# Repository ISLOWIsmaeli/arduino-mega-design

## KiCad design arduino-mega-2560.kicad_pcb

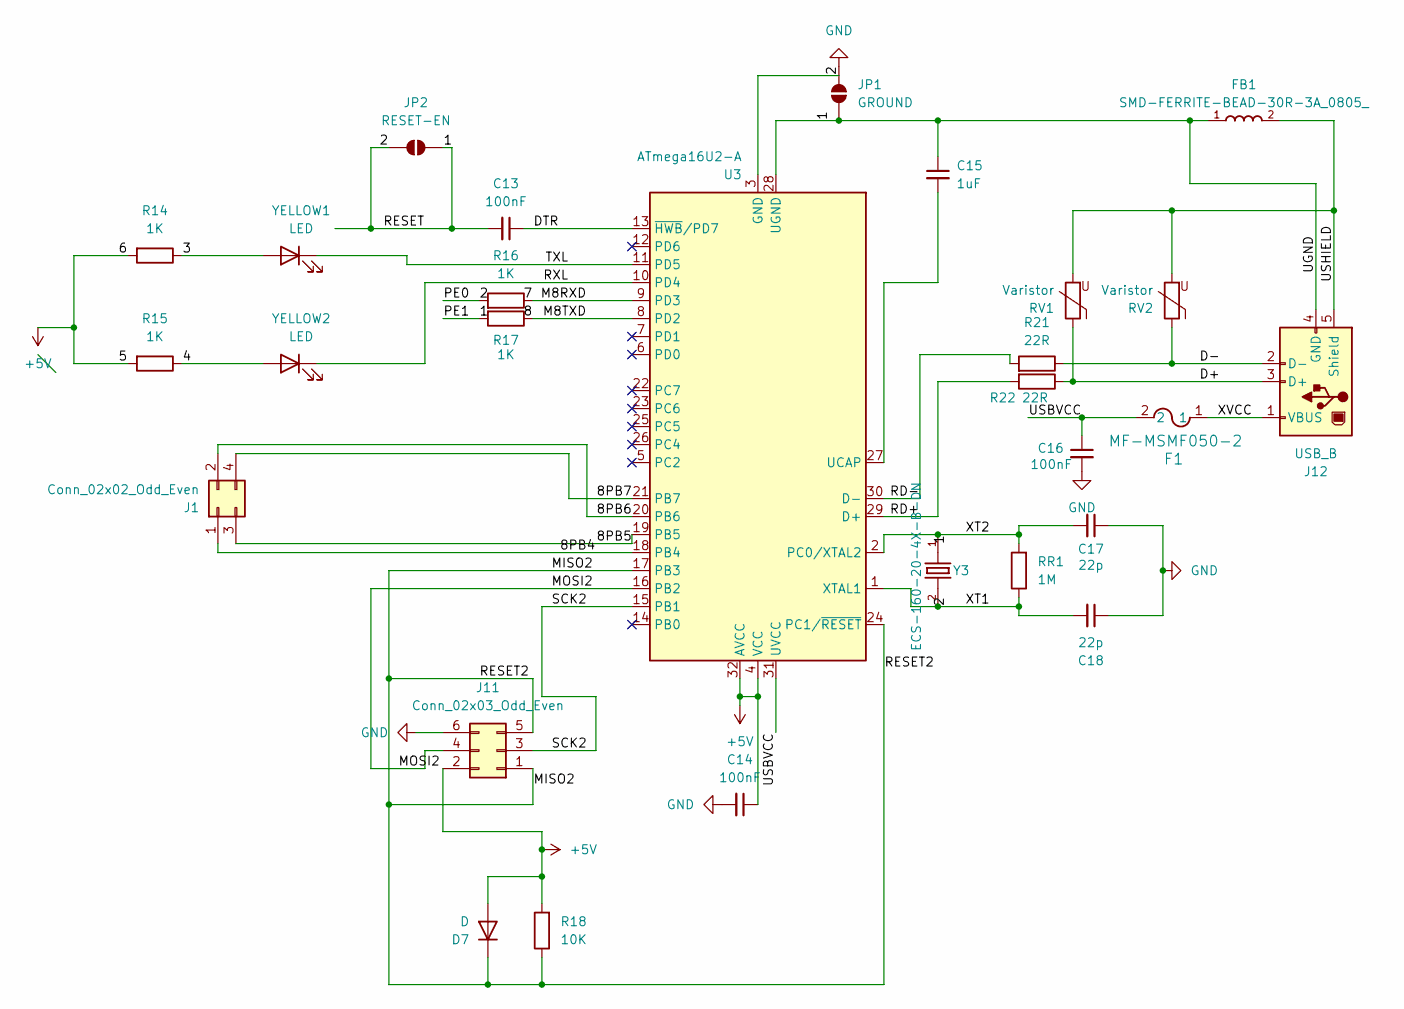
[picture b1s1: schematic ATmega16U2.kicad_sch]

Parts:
C13, C14, C16: 100nF; C_0402_1005Metric_Pad0.74x0.62mm_HandSolder
C15: 1uF; C_0402_1005Metric_Pad0.74x0.62mm_HandSolder
C17, C18: 22p; C_0402_1005Metric_Pad0.74x0.62mm_HandSolder
D7: D; D_0603_1608Metric
F1: MF-MSMF050-2; FUSE_F050-2
FB1: SMD-FERRITE-BEAD-30R-3A_0805_; L0805; MPN MH2029-300Y
J1: Conn_02x02_Odd_Even; PinHeader_2x02_P1.00mm_Vertical
J11: Conn_02x03_Odd_Even; PinHeader_2x03_P1.00mm_Vertical
J12: USB_B; USB_B_OST_USB-B1HSxx_Horizontal
JP1: GROUND; SolderJumper-2_P1.3mm_Open_RoundedPad1.0x1.5mm
JP2: RESET-EN; SolderJumper-2_P1.3mm_Open_RoundedPad1.0x1.5mm
R14, R15, R16, R17: 1K; R_0201_0603Metric_Pad0.64x0.40mm_HandSolder
R18: 10K; R_0201_0603Metric_Pad0.64x0.40mm_HandSolder
R21, R22: 22R; R_0201_0603Metric_Pad0.64x0.40mm_HandSolder
RR1: 1M; R_0201_0603Metric_Pad0.64x0.40mm_HandSolder
RV1, RV2: Varistor; R_0201_0603Metric_Pad0.64x0.40mm_HandSolder
U3: ATmega16U2-A; TQFP-32_7x7mm_P0.8mm
Y3: ECS-160-20-4X-B-DN; XTAL_ECS-160-20-4X-B-DN
YELLOW1, YELLOW2: LED; LED_0201_0603Metric

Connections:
+5V: C14.1, D7.2 (A), J11.2, R14.2, R15.2, R18.2, U3.4 (VCC), U3.32 (AVCC); also elsewhere on the board
/ATmega16U2/1: C13.2, C15.1, C17.2, C18.2, FB1.1, J12.4 (GND), JP1.1 (A), JP2.1 (A), JP2.2 (B), R16.2, R17.2, RR1.1, RR1.2, U3.1 (XTAL1), U3.2 (PC0/XTAL2), U3.3 (GND), U3.28 (UGND), Y3.1, Y3.2; also elsewhere on the board
/ATmega16U2/3: R14.1, YELLOW1.2 (A)
/ATmega16U2/4: R15.1, YELLOW2.2 (A)
/ATmega16U2/7: R16.1, U3.9 (PD3)
/ATmega16U2/8: R17.1, U3.8 (PD2)
/ATmega16U2/8PB4: J1.1, U3.18 (PB4)
/ATmega16U2/8PB5: J1.3, U3.19 (PB5)
/ATmega16U2/8PB6: J1.2, U3.20 (PB6)
/ATmega16U2/8PB7: J1.4, U3.21 (PB7)
/ATmega16U2/D+: J12.3 (D+), R22.1, RV1.1
/ATmega16U2/D-: J12.2 (D-), R21.1, RV2.1
/ATmega16U2/DTR: C13.1, U3.13 (~HWB/PD7)
/ATmega16U2/MISO2: D7.1 (K), J11.1, J11.5, R18.1, U3.17 (PB3), U3.24 (PC1/~RESET)
/ATmega16U2/MOSI2: J11.4, U3.16 (PB2)
/ATmega16U2/RD+: R22.2, U3.29 (D+)
/ATmega16U2/RD-: R21.2, U3.30 (D-)
/ATmega16U2/RXL: U3.10 (PD4), YELLOW2.1 (K)
/ATmega16U2/SCK2: J11.3, U3.15 (PB1)
/ATmega16U2/TXL: U3.11 (PD5), YELLOW1.1 (K)
/ATmega16U2/USBVCC: C16.1, F1.2, U3.31 (UVCC)
/ATmega16U2/USHIELD: FB1.2, J12.5 (Shield), RV1.2, RV2.2
/ATmega16U2/XVCC: F1.1, J12.1 (VBUS)
GND: C14.2, C16.2, C17.1, C18.1, J11.6, JP1.2 (B); also elsewhere on the board
unnamed: C15.2, U3.27 (UCAP)

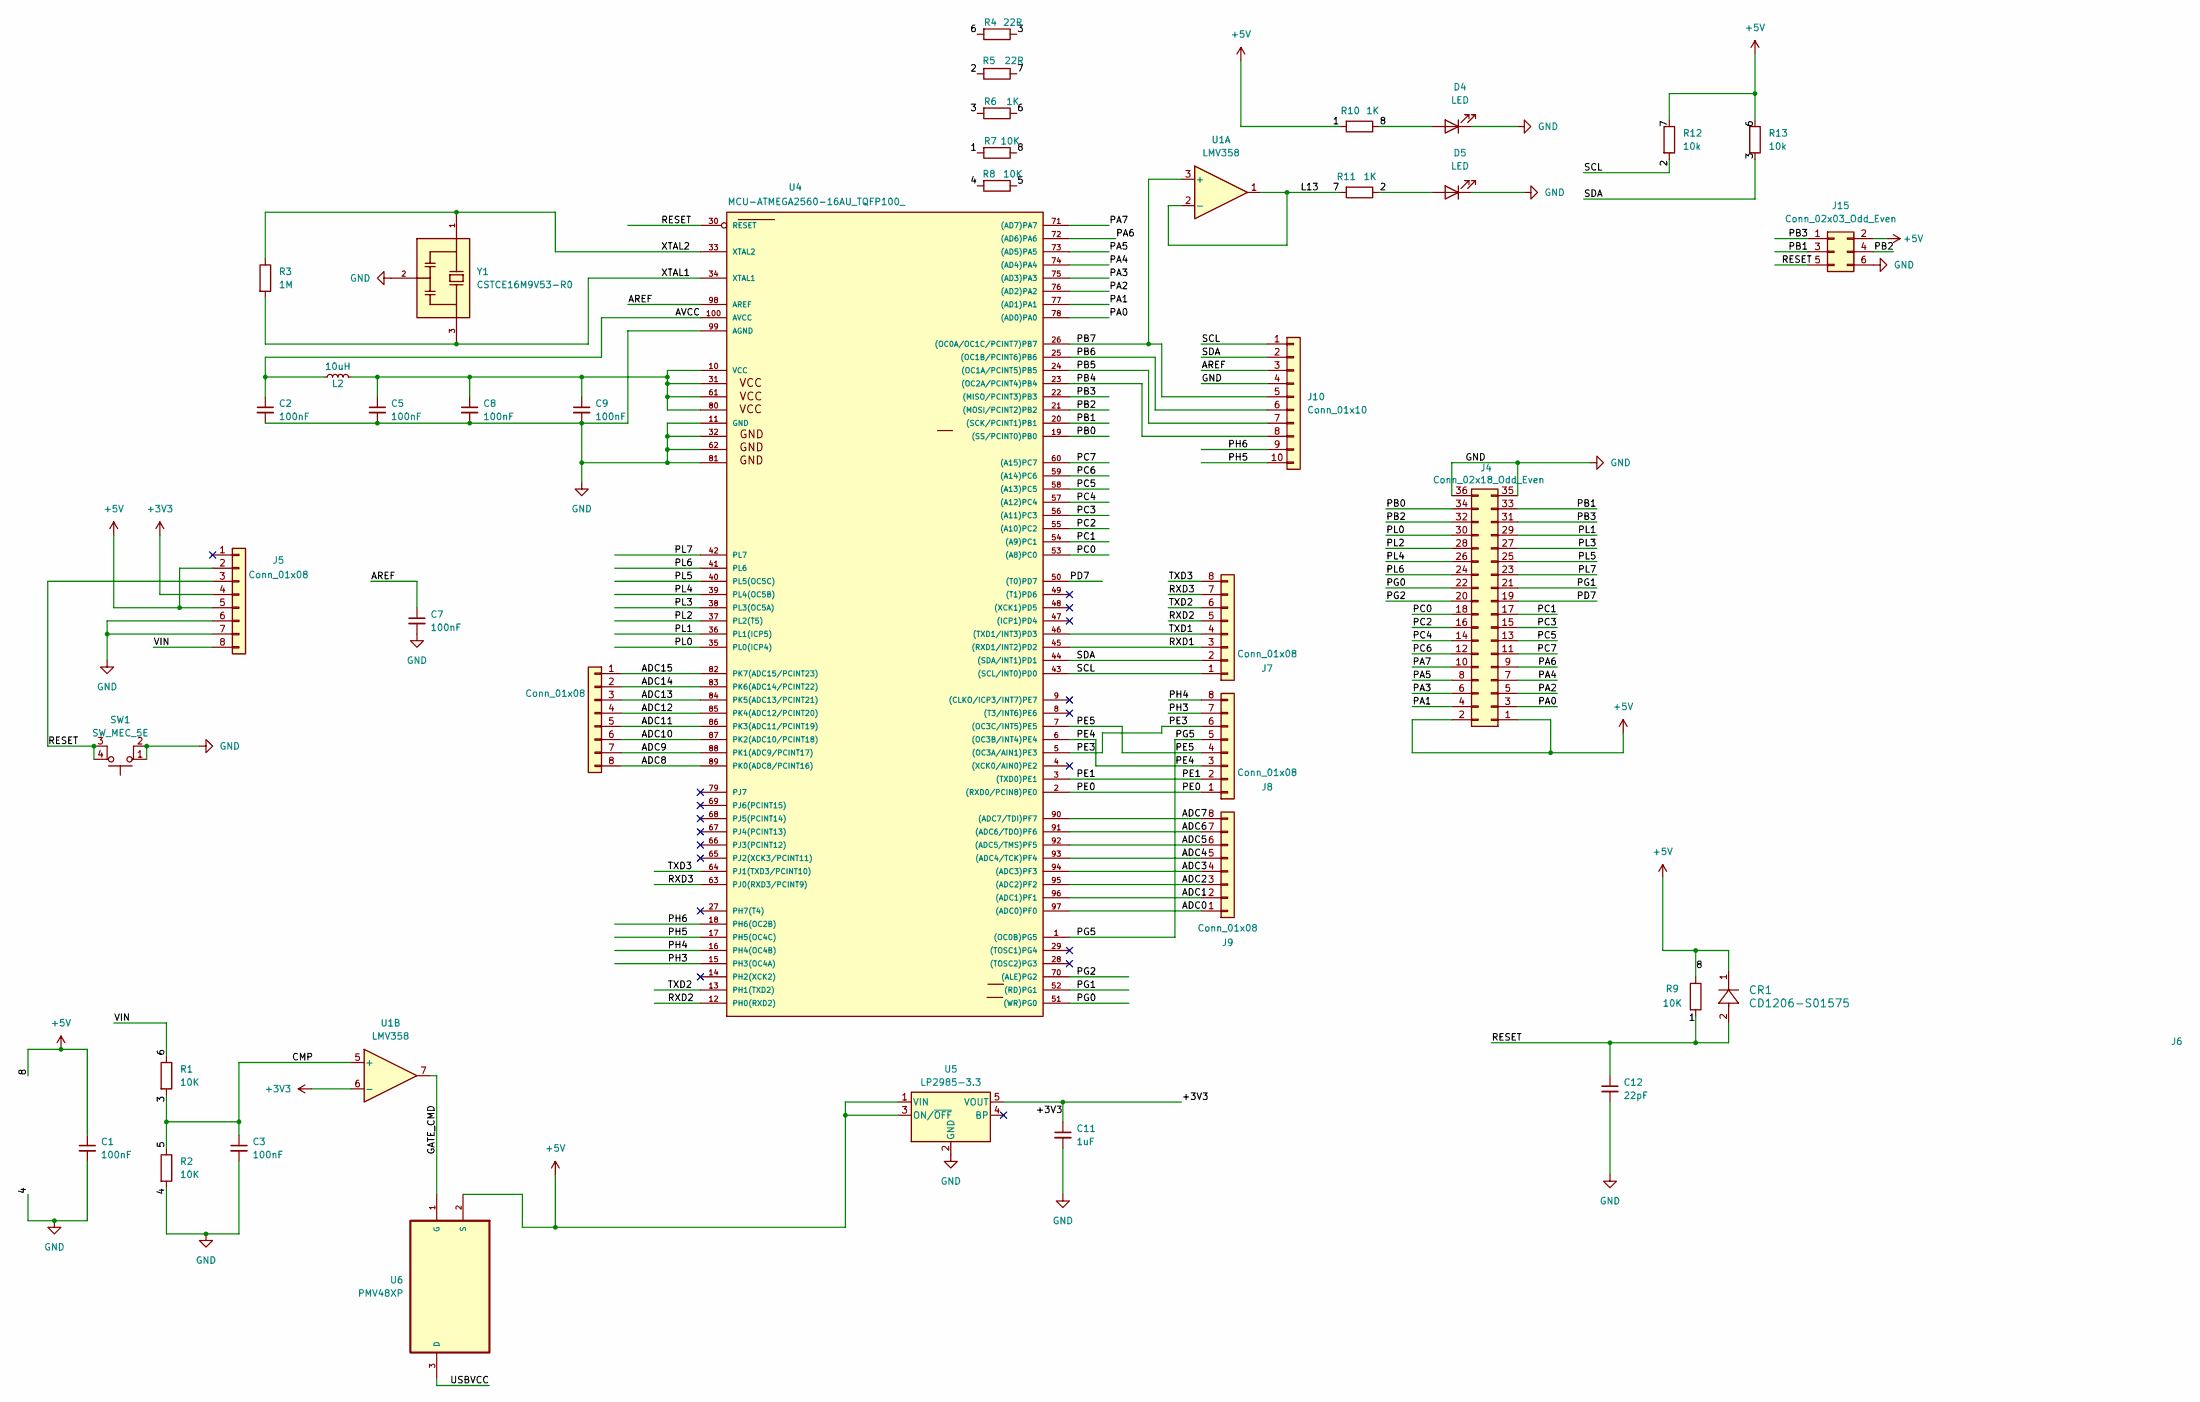
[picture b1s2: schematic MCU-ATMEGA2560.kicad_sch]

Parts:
C1, C2, C3, C5, C7, C8, C9: 100nF; C_0402_1005Metric_Pad0.74x0.62mm_HandSolder
C11: 1uF; C_0402_1005Metric_Pad0.74x0.62mm_HandSolder
C12: 22pF; C_0402_1005Metric_Pad0.74x0.62mm_HandSolder
CR1: CD1206-S01575; D_0603_1608Metric
D4, D5: LED; LED_0201_0603Metric_Pad0.64x0.40mm_HandSolder
J4: Conn_02x18_Odd_Even; PinSocket_2x18_P2.00mm_Vertical
J5, J6, J7, J8, J9: Conn_01x08; PinHeader_1x08_P1.27mm_Vertical
J10: Conn_01x10; PinSocket_1x10_P1.27mm_Vertical
J15: Conn_02x03_Odd_Even; PinHeader_2x03_P1.00mm_Vertical
L2: 10uH; L_0201_0603Metric_Pad0.64x0.40mm_HandSolder
R1, R2, R7, R8, R9: 10K; R_0201_0603Metric_Pad0.64x0.40mm_HandSolder
R3: 1M; R_0201_0603Metric
R4, R5: 22R; R_0201_0603Metric_Pad0.64x0.40mm_HandSolder
R6, R10, R11: 1K; R_0201_0603Metric_Pad0.64x0.40mm_HandSolder
R12, R13: 10k; R_0201_0603Metric_Pad0.64x0.40mm_HandSolder
SW1: SW_MEC_5E; SW_Push_1P1T_NO_CK_KSC6xxJ
U1: LMV358; MSOP-8-1EP_3x3mm_P0.65mm_EP2.5x3mm_Mask1.73x2.36mm
U4: MCU-ATMEGA2560-16AU_TQFP100_; QFP50P1600X1600X120-100N; MPN ATMEGA2560-16AU; DigiKey_Part_Number ATMEGA2560-16AU-ND
U5: LP2985-3.3; SOT-23-5
U6: PMV48XP; SOT95P230X110-3N; MPN PMV48XP
Y1: CSTCE16M9V53-R0; OSC_CSTCE16M9V53-R0; PARTREV May 7, 2019

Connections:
+3V3: C11.1, J5.4, U1.6 (-), U5.5 (VOUT)
+5V: C1.1, C12.1, CR1.1, CR1.2, D4.2 (A), J4.1, J4.2, J5.2, J5.3, J5.5, J5.8, J15.2, J15.5, R1.1, R4.2, R5.1, R6.1, R7.1, R7.2, R9.1, R9.2, R10.1, R10.2, R11.2, R12.1, R13.1, SW1.3 (K), SW1.4 (A), U1.1, U1.2 (-), U4.30 (RESET), U5.1 (VIN), U5.3 (ON/~OFF), U6.2 (S); also elsewhere on the board
/MCU-ATMEGA2560/2: D5.2 (A), J7.1, J10.1, R5.2, R11.1, R12.2, U4.43 ((SCL/INT0)PD0)
/MCU-ATMEGA2560/3: C3.1, J7.2, J10.2, R1.2, R2.1, R4.1, R6.2, R8.1, R13.2, U1.5 (+), U4.44 ((SDA/INT1)PD1)
/MCU-ATMEGA2560/ADC0: J9.1, U4.97 ((ADC0)PF0)
/MCU-ATMEGA2560/ADC1: J9.2, U4.96 ((ADC1)PF1)
/MCU-ATMEGA2560/ADC2: J9.3, U4.95 ((ADC2)PF2)
/MCU-ATMEGA2560/ADC3: J9.4, U4.94 ((ADC3)PF3)
/MCU-ATMEGA2560/ADC4: J9.5, U4.93 ((ADC4/TCK)PF4)
/MCU-ATMEGA2560/ADC5: J9.6, U4.92 ((ADC5/TMS)PF5)
/MCU-ATMEGA2560/ADC6: J9.7, U4.91 ((ADC6/TDO)PF6)
/MCU-ATMEGA2560/ADC7: J9.8, U4.90 ((ADC7/TDI)PF7)
/MCU-ATMEGA2560/ADC8: J6.8, U4.89 (PK0(ADC8/PCINT16))
/MCU-ATMEGA2560/ADC9: J6.7, U4.88 (PK1(ADC9/PCINT17))
/MCU-ATMEGA2560/ADC10: J6.6, U4.87 (PK2(ADC10/PCINT18))
/MCU-ATMEGA2560/ADC11: J6.5, U4.86 (PK3(ADC11/PCINT19))
/MCU-ATMEGA2560/ADC12: J6.4, U4.85 (PK4(ADC12/PCINT20))
/MCU-ATMEGA2560/ADC13: J6.3, U4.84 (PK5(ADC13/PCINT21))
/MCU-ATMEGA2560/ADC14: J6.2, U4.83 (PK6(ADC14/PCINT22))
/MCU-ATMEGA2560/ADC15: J6.1, U4.82 (PK7(ADC15/PCINT23))
/MCU-ATMEGA2560/AREF: C7.1, J10.3, U4.98 (AREF)
/MCU-ATMEGA2560/AVCC: C2.1, L2.1, U4.100 (AVCC)
/MCU-ATMEGA2560/GATE_CMD: U1.7, U6.1 (G)
/MCU-ATMEGA2560/PA0: J4.3, U4.78 ((AD0)PA0)
/MCU-ATMEGA2560/PA1: J4.4, U4.77 ((AD1)PA1)
/MCU-ATMEGA2560/PA2: J4.5, U4.76 ((AD2)PA2)
/MCU-ATMEGA2560/PA3: J4.6, U4.75 ((AD3)PA3)
/MCU-ATMEGA2560/PA4: J4.7, U4.74 ((AD4)PA4)
/MCU-ATMEGA2560/PA5: J4.8, U4.73 ((AD5)PA5)
/MCU-ATMEGA2560/PA6: J4.9, U4.72 ((AD6)PA6)
/MCU-ATMEGA2560/PA7: J4.10, U4.71 ((AD7)PA7)
/MCU-ATMEGA2560/PB0: J4.34, U4.19 ((SS/PCINT0)PB0)
/MCU-ATMEGA2560/PB1: J4.33, J15.3, U4.20 ((SCK/PCINT1)PB1)
/MCU-ATMEGA2560/PB2: J4.32, J15.4, U4.21 ((MOSI/PCINT2)PB2)
/MCU-ATMEGA2560/PB3: J4.31, J15.1, U4.22 ((MISO/PCINT3)PB3)
/MCU-ATMEGA2560/PB4: J10.8, U4.23 ((OC2A/PCINT4)PB4)
/MCU-ATMEGA2560/PB5: J10.7, U4.24 ((OC1A/PCINT5)PB5)
/MCU-ATMEGA2560/PB6: J10.6, U4.25 ((OC1B/PCINT6)PB6)
/MCU-ATMEGA2560/PB7: J10.5, U1.3 (+), U4.26 ((OC0A/OC1C/PCINT7)PB7)
/MCU-ATMEGA2560/PC0: J4.18, U4.53 ((A8)PC0)
/MCU-ATMEGA2560/PC1: J4.17, U4.54 ((A9)PC1)
/MCU-ATMEGA2560/PC2: J4.16, U4.55 ((A10)PC2)
/MCU-ATMEGA2560/PC3: J4.15, U4.56 ((A11)PC3)
/MCU-ATMEGA2560/PC4: J4.14, U4.57 ((A12)PC4)
/MCU-ATMEGA2560/PC5: J4.13, U4.58 ((A13)PC5)
/MCU-ATMEGA2560/PC6: J4.12, U4.59 ((A14)PC6)
/MCU-ATMEGA2560/PC7: J4.11, U4.60 ((A15)PC7)
/MCU-ATMEGA2560/PD7: J4.19, U4.50 ((T0)PD7)
/MCU-ATMEGA2560/PE0: J8.1, U4.2 ((RXD0/PCIN8)PE0)
/MCU-ATMEGA2560/PE1: J8.2, U4.3 ((TXD0)PE1)
/MCU-ATMEGA2560/PE3: J8.6, U4.5 ((OC3A/AIN1)PE3)
/MCU-ATMEGA2560/PG0: J4.22, U4.51 ((WR)PG0)
/MCU-ATMEGA2560/PG1: J4.21, U4.52 ((RD)PG1)
/MCU-ATMEGA2560/PG2: J4.20, U4.70 ((ALE)PG2)
/MCU-ATMEGA2560/PH3: J8.7, U4.15 (PH3(OC4A))
/MCU-ATMEGA2560/PH4: J8.8, U4.16 (PH4(OC4B))
/MCU-ATMEGA2560/PH5: J10.10, U4.17 (PH5(OC4C))
/MCU-ATMEGA2560/PH6: J10.9, U4.18 (PH6(OC2B))
/MCU-ATMEGA2560/PL0: J4.30, U4.35 (PL0(ICP4))
/MCU-ATMEGA2560/PL1: J4.29, U4.36 (PL1(ICP5))
/MCU-ATMEGA2560/PL2: J4.28, U4.37 (PL2(T5))
/MCU-ATMEGA2560/PL3: J4.27, U4.38 (PL3(OC5A))
/MCU-ATMEGA2560/PL4: J4.26, U4.39 (PL4(OC5B))
/MCU-ATMEGA2560/PL5: J4.25, U4.40 (PL5(OC5C))
/MCU-ATMEGA2560/PL6: J4.24, U4.41 (PL6)
/MCU-ATMEGA2560/PL7: J4.23, U4.42 (PL7)
/MCU-ATMEGA2560/RXD1: J7.3, U4.45 ((RXD1/INT2)PD2)
/MCU-ATMEGA2560/RXD2: J7.5, U4.12 (PH0(RXD2))
/MCU-ATMEGA2560/RXD3: J7.7, U4.63 (PJ0(RXD3/PCINT9))
/MCU-ATMEGA2560/TXD1: J7.4, U4.46 ((TXD1/INT3)PD3)
/MCU-ATMEGA2560/TXD2: J7.6, U4.13 (PH1(TXD2))
/MCU-ATMEGA2560/TXD3: J7.8, U4.64 (PJ1(TXD3/PCINT10))
/MCU-ATMEGA2560/USBVCC: U6.3 (D)
/MCU-ATMEGA2560/XTAL1: R3.2, U4.34 (XTAL1), Y1.3
/MCU-ATMEGA2560/XTAL2: R3.1, U4.33 (XTAL2), Y1.1
GND: C1.2, C2.2, C3.2, C5.2, C7.2, C8.2, C9.2, C11.2, C12.2, D4.1 (K), D5.1 (K), J4.35, J4.36, J5.6, J5.7, J10.4, J15.6, R2.2, R8.2, SW1.1, SW1.2, U4.11 (GND), U4.32, U4.62, U4.81, U4.99 (AGND), U5.2 (GND), Y1.2; also elsewhere on the board
unnamed: C5.1, C8.1, C9.1, L2.2, U4.10 (VCC), U4.31, U4.61, U4.80

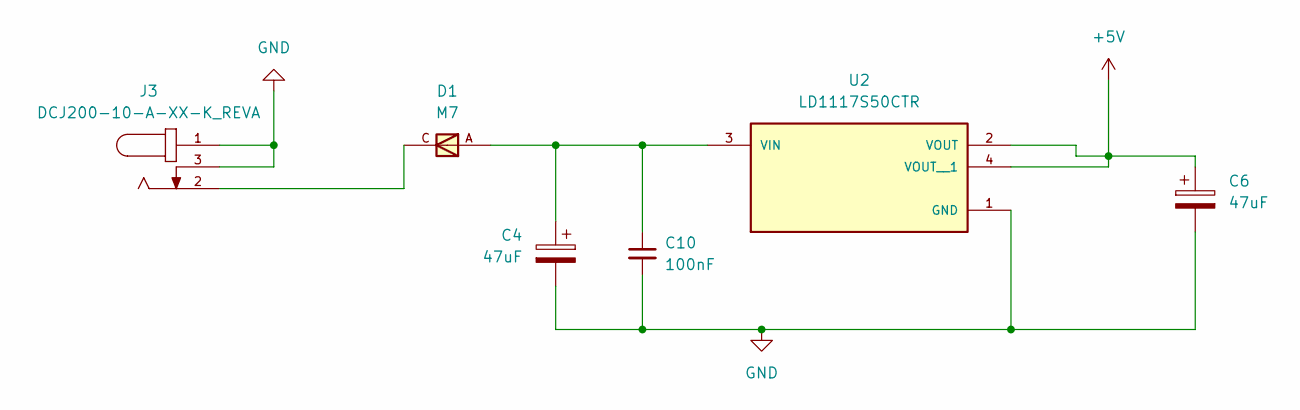
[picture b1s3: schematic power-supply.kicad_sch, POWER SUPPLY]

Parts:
C4, C6: 47uF; CP_Elec_4x3
C10: 100nF; C_0402_1005Metric_Pad0.74x0.62mm_HandSolder
D1: M7; DIOM505270X240; MPN M7
J3: DCJ200-10-A-XX-K_REVA; BarrelJack_GCT_DCJ200-10-A_Horizontal; PARTREV A
U2: LD1117S50CTR; SOT230P700X180-4N; PARTREV 37

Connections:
+5V: C6.1, U2.2 (VOUT), U2.4 (VOUT__1); also elsewhere on the board
GND: C4.2, C6.2, C10.2, J3.1, J3.3, U2.1 (GND); also elsewhere on the board
unnamed: D1.C, J3.2
unnamed: C4.1, C10.1, D1.A, U2.3 (VIN)

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
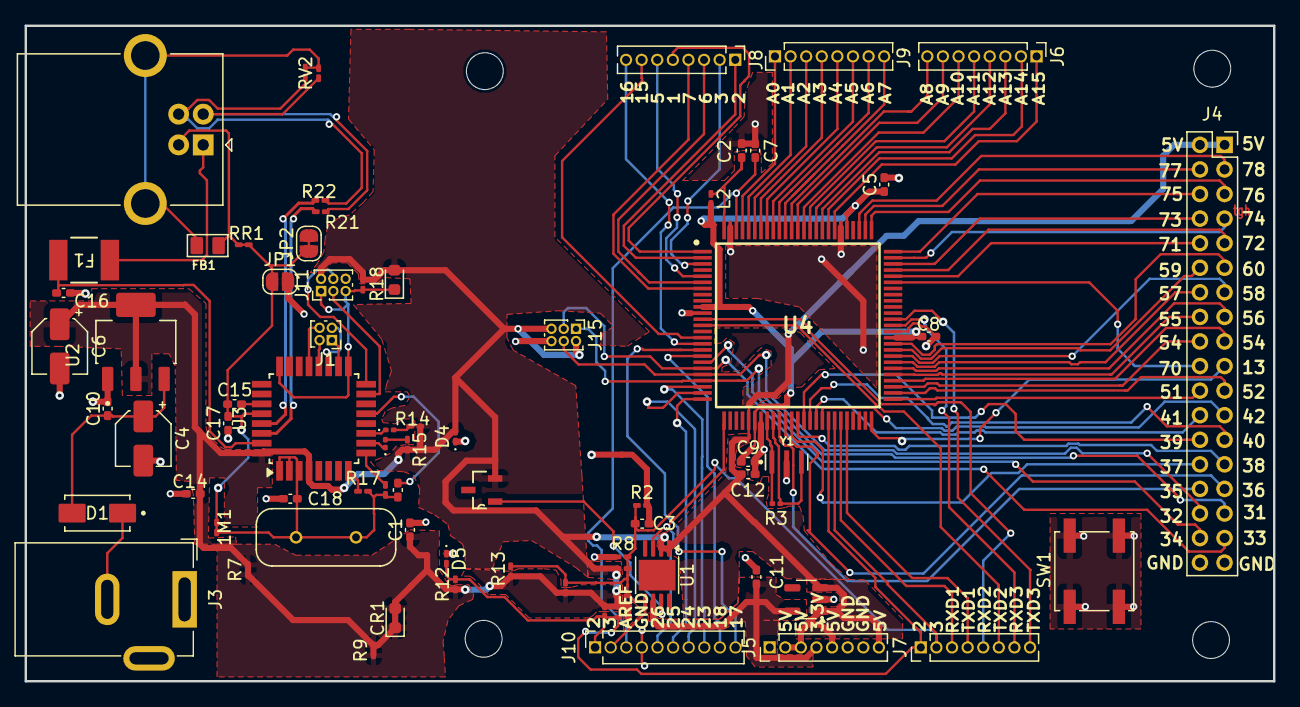
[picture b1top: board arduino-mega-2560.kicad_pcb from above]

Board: 2 copper layers, 101.6 x 53.3 mm, 79 parts (0 on the bottom side), 104 nets.

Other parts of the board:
1M1: R; R_0201_0603Metric_Pad0.64x0.40mm_HandSolder
H2, H3, H4, H5: MountingHole; MountingHole_3mm

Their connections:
/ATmega16U2/1: 1M1.1, 1M1.2; also elsewhere on the board

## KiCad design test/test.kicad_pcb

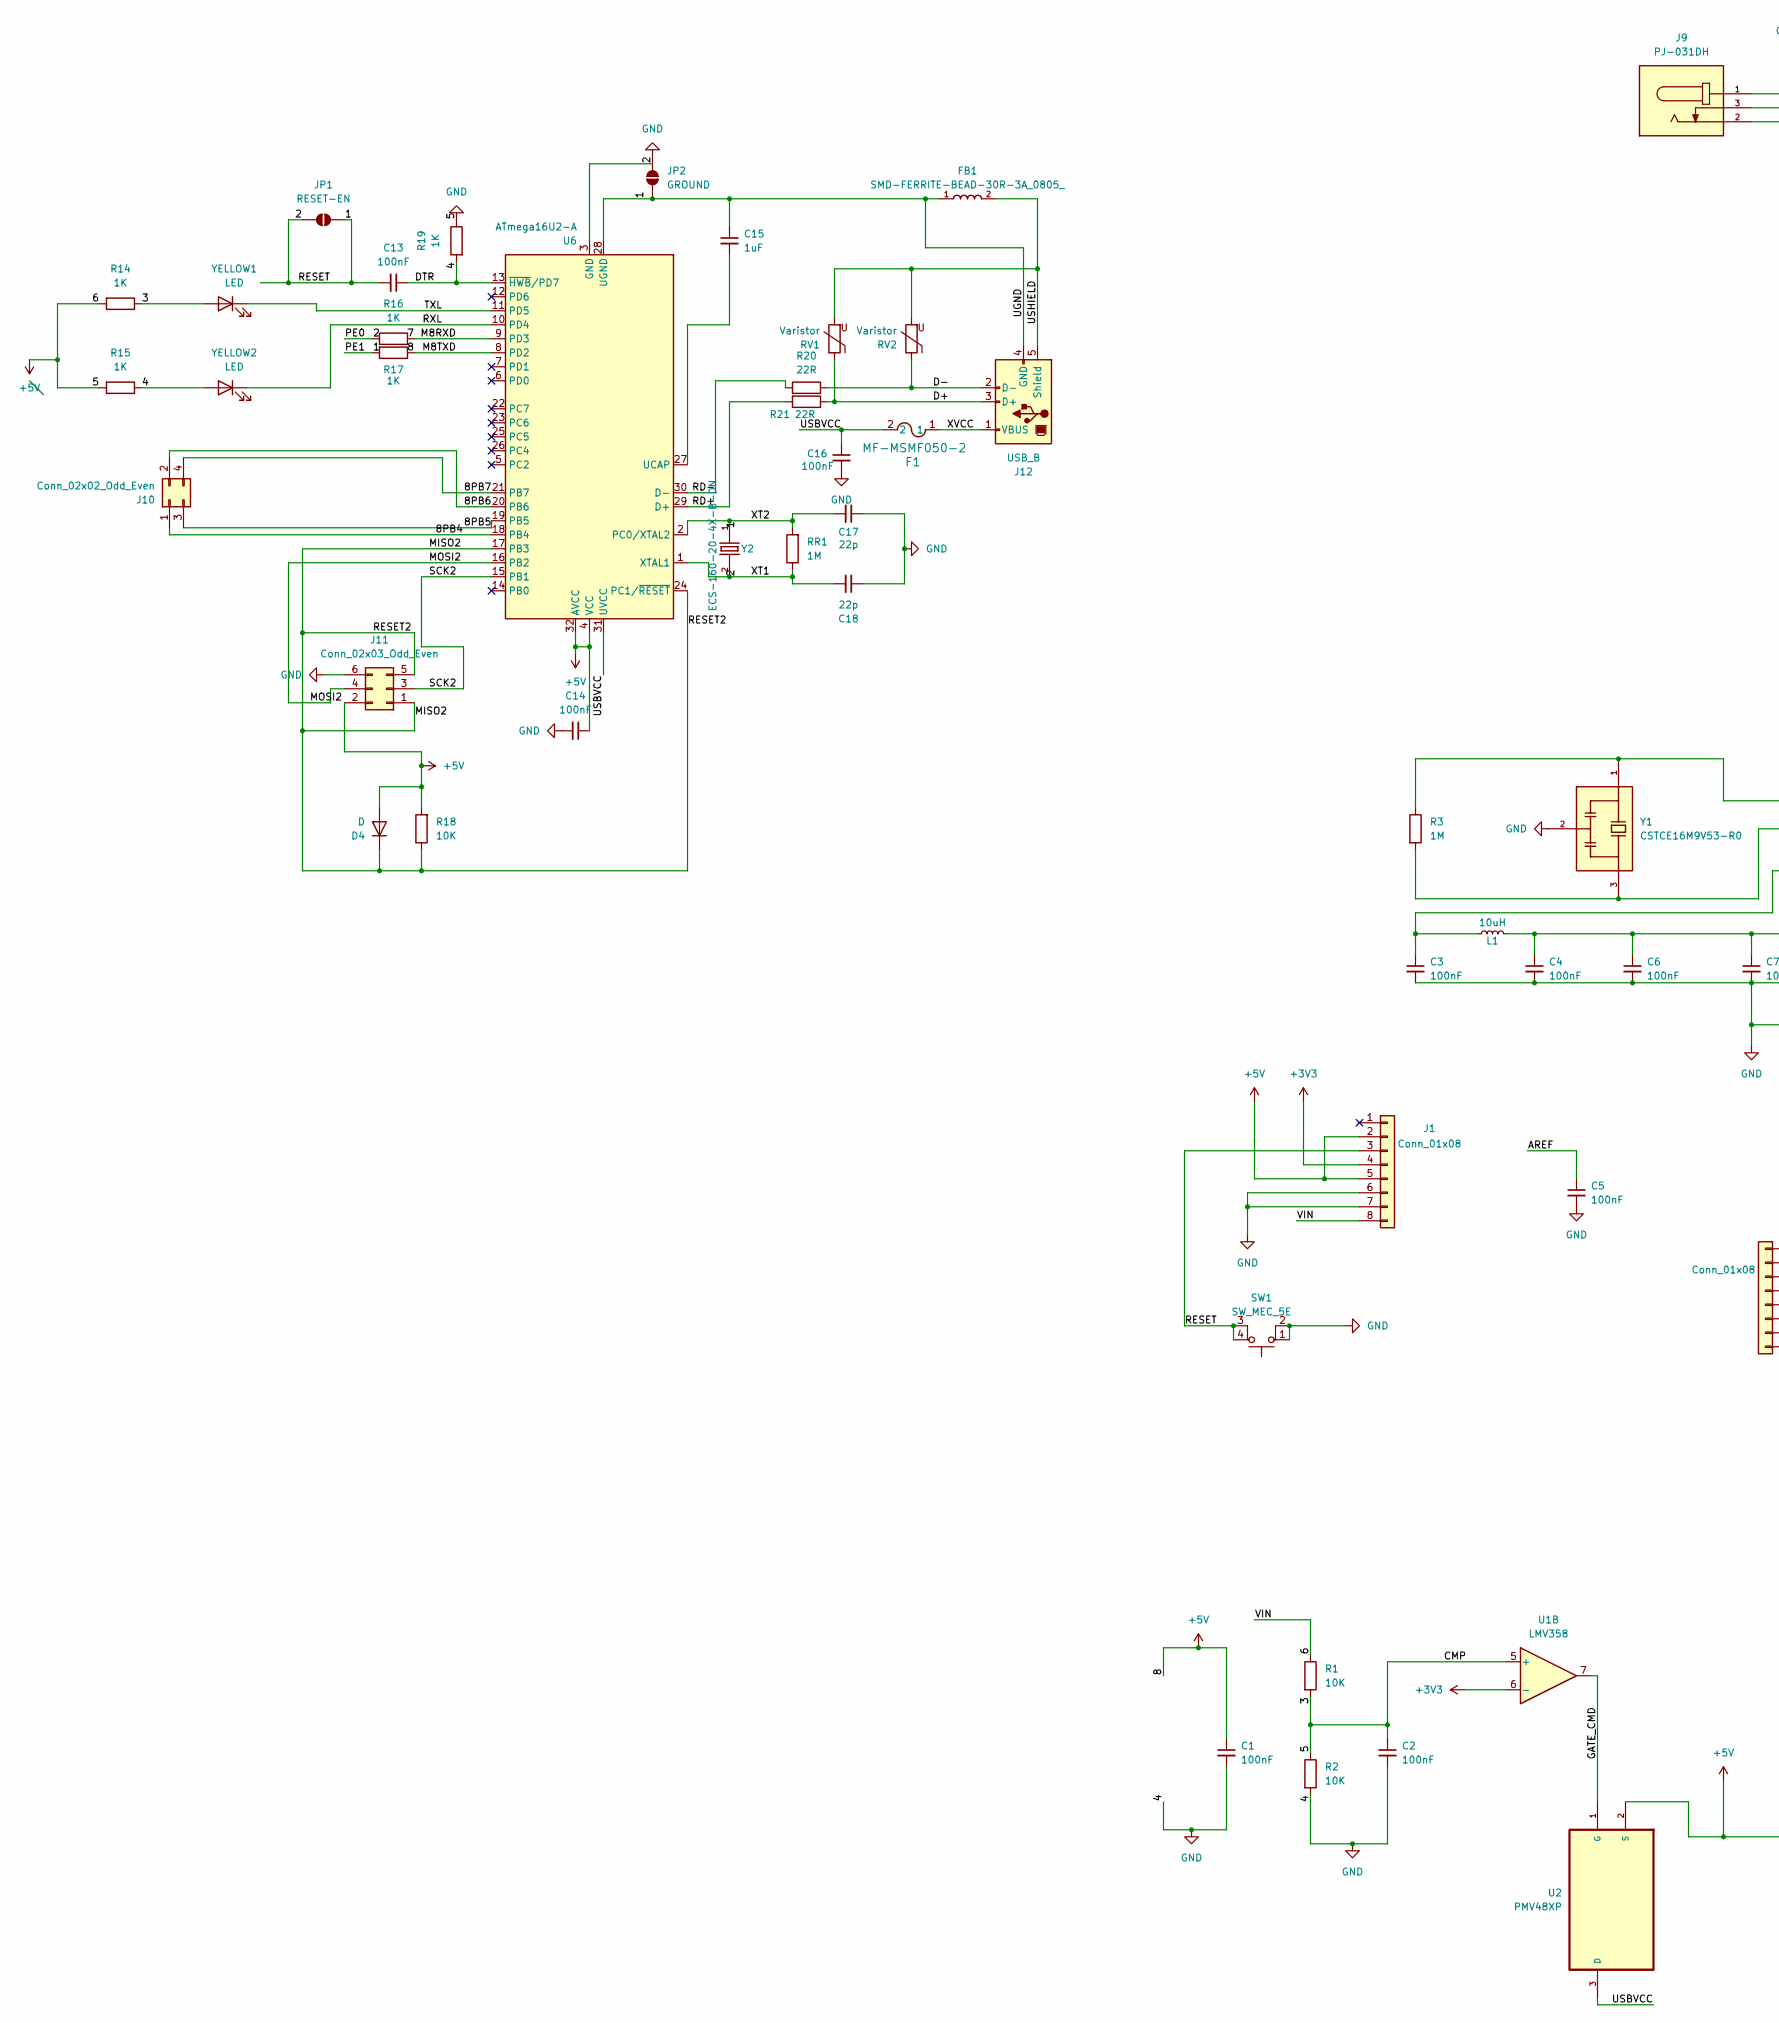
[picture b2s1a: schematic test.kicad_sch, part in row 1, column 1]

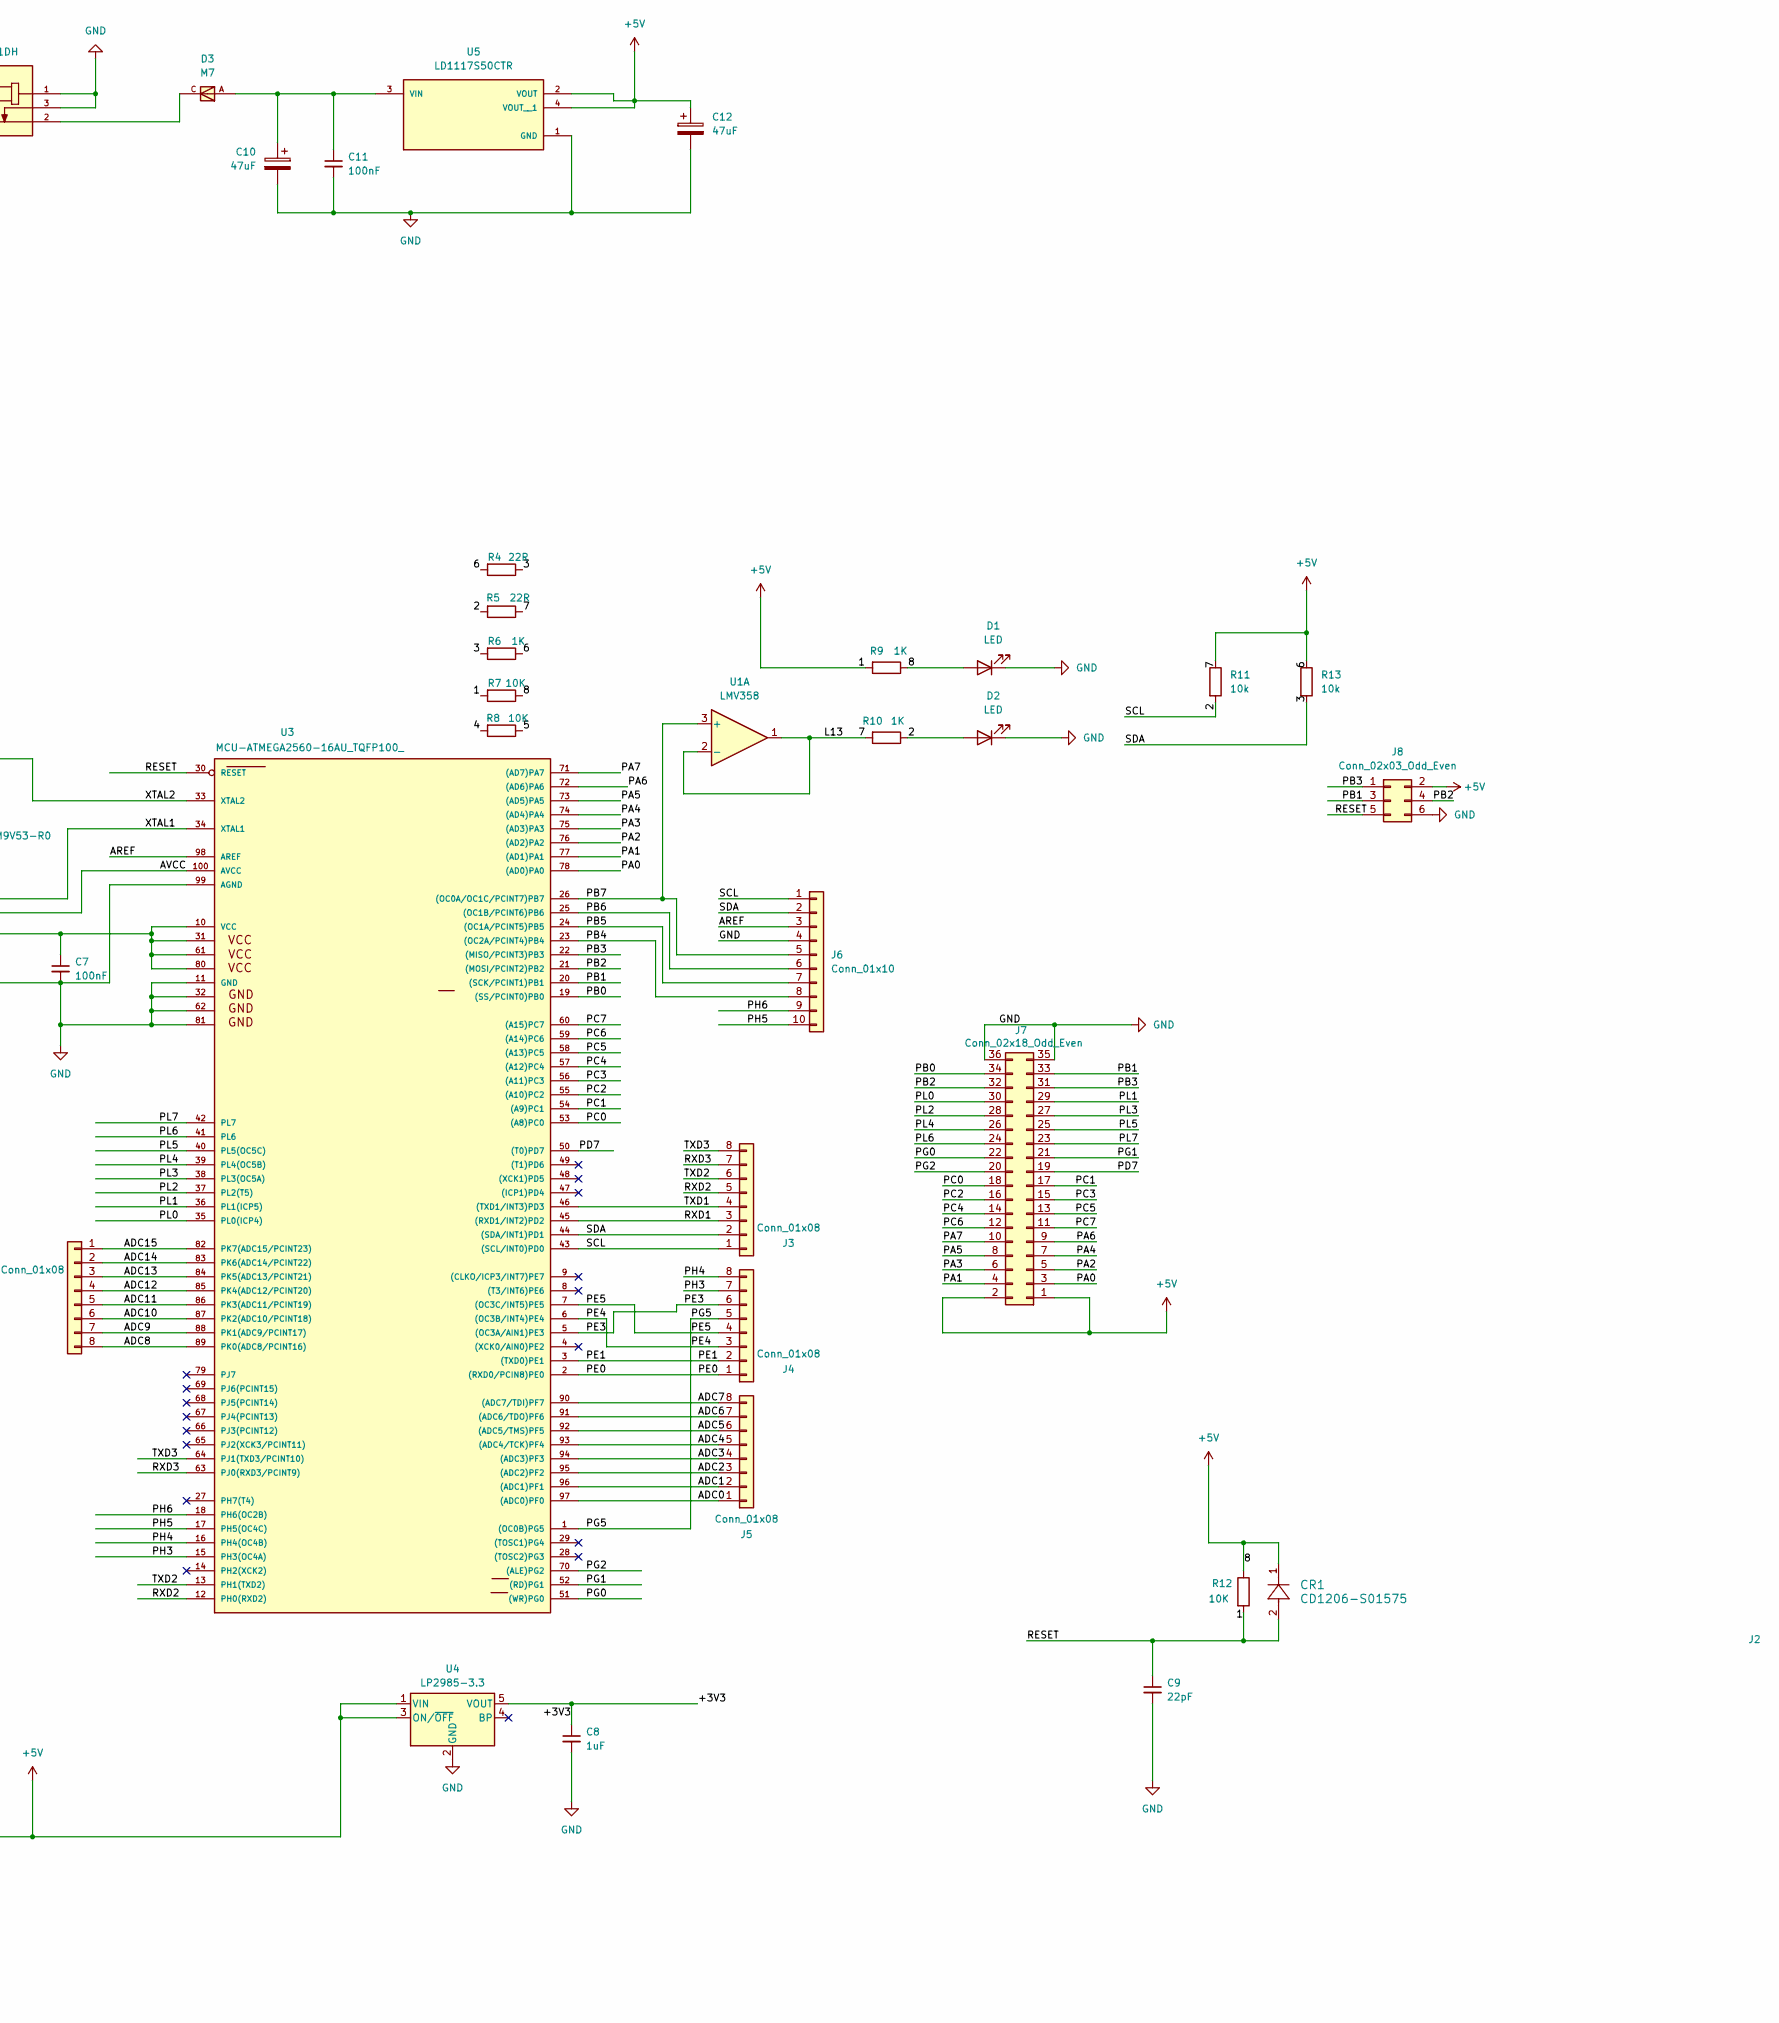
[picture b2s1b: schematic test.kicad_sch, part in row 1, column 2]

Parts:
C1, C2, C3, C4, C5, C6, C7, C11, C13, C14, C16: 100nF; C_0402_1005Metric_Pad0.74x0.62mm_HandSolder
C8, C15: 1uF; C_0402_1005Metric_Pad0.74x0.62mm_HandSolder
C9: 22pF; C_0402_1005Metric_Pad0.74x0.62mm_HandSolder
C10, C12: 47uF; CP_Elec_4x3
C17, C18: 22p; C_0402_1005Metric_Pad0.74x0.62mm_HandSolder
CR1: CD1206-S01575; DIODE_CD1206-S01575_BRN
D1, D2: LED; LED_0201_0603Metric_Pad0.64x0.40mm_HandSolder
D3: M7; DIOM505270X240; MPN M7
D4: D; D_0402_1005Metric_Pad0.77x0.64mm_HandSolder
F1: MF-MSMF050-2; FUSE_F050-2
FB1: SMD-FERRITE-BEAD-30R-3A_0805_; L0805; MPN MH2029-300Y
J1, J2, J3, J4, J5: Conn_01x08; PinSocket_1x08_P1.00mm_Vertical
J6: Conn_01x10; PinSocket_1x10_P1.00mm_Vertical
J7: Conn_02x18_Odd_Even; PinSocket_2x18_P1.27mm_Vertical
J8, J11: Conn_02x03_Odd_Even; PinHeader_2x03_P1.00mm_Vertical
J9: PJ-031DH; CUI_PJ-031DH; PARTREV 1.05
J10: Conn_02x02_Odd_Even; PinHeader_2x02_P1.00mm_Vertical
J12: USB_B; USB_B_OST_USB-B1HSxx_Horizontal
JP1: RESET-EN; SolderJumper-2_P1.3mm_Open_RoundedPad1.0x1.5mm
JP2: GROUND; SolderJumper-2_P1.3mm_Open_RoundedPad1.0x1.5mm
L1: 10uH; L_0201_0603Metric_Pad0.64x0.40mm_HandSolder
R1, R2, R7, R8, R12, R18: 10K; R_0201_0603Metric_Pad0.64x0.40mm_HandSolder
R3: 1M; R_0201_0603Metric
R4, R5, R20, R21: 22R; R_0201_0603Metric_Pad0.64x0.40mm_HandSolder
R6, R9, R10, R14, R15, R16, R17, R19: 1K; R_0201_0603Metric_Pad0.64x0.40mm_HandSolder
R11, R13: 10k; R_0201_0603Metric_Pad0.64x0.40mm_HandSolder
RR1: 1M; R_0201_0603Metric_Pad0.64x0.40mm_HandSolder
RV1, RV2: Varistor; R_0201_0603Metric_Pad0.64x0.40mm_HandSolder
SW1: SW_MEC_5E; SW_Push_1P1T_NO_CK_KSC6xxJ
U1: LMV358; MSOP-8-1EP_3x3mm_P0.65mm_EP2.5x3mm_Mask1.73x2.36mm_ThermalV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
U2: PMV48XP; SOT95P230X110-3N; MPN PMV48XP
U3: MCU-ATMEGA2560-16AU_TQFP100_; TQFP100-0.5-14X14MM; MPN ATMEGA2560-16AU; DigiKey_Part_Number ATMEGA2560-16AU-ND
U4: LP2985-3.3; SOT-23-5
U5: LD1117S50CTR; SOT230P700X180-4N; PARTREV 37
U6: ATmega16U2-A; TQFP-32_7x7mm_P0.8mm
Y1: CSTCE16M9V53-R0; OSC_CSTCE16M9V53-R0; PARTREV May 7, 2019
Y2: ECS-160-20-4X-B-DN; XTAL_ECS-160-20-4X-B-DN
YELLOW1, YELLOW2: LED; LED_0201_0603Metric

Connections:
+3V3: C8.1, J1.4, U1.6 (-), U4.5 (VOUT)
+5V: C1.1, C1.2, C2.1, C2.2, C3.2, C4.2, C5.2, C6.2, C7.2, C8.2, C9.1, C9.2, C10.2, C11.2, C12.1, C12.2, C13.1, C13.2, C14.1, C14.2, C15.1, C16.2, C17.1, C17.2, C18.1, C18.2, CR1.1, CR1.2, D1.1 (K), D1.2 (A), D2.1 (K), D2.2 (A), D4.2 (A), FB1.1, J1.2, J1.3, J1.5, J1.6, J1.7, J1.8, J3.1, J3.2, J4.1, J4.2, J6.1, J6.2, J6.4, J7.1, J7.2, J7.35, J7.36, J8.2, J8.5, J8.6, J9.1, J9.3, J11.2, J11.6, J12.4 (GND), JP1.1 (A), JP1.2 (B), JP2.1 (A), JP2.2 (B), R1.1, R1.2, R2.1, R2.2, R4.1, R4.2, R5.1, R5.2, R6.1, R6.2, R7.1, R7.2, R8.1, R8.2, R9.1, R9.2, R10.1, R10.2, R11.1, R11.2, R12.1, R12.2, R13.1, R13.2, R14.1, R14.2, R15.1, R15.2, R16.1, R16.2, R17.1, R17.2, R18.2, R19.1, R19.2, RR1.1, RR1.2, SW1.1, SW1.2, SW1.3 (K), SW1.4 (A), U1.1, U1.2 (-), U1.5 (+), U2.2 (S), U3.2 ((RXD0/PCIN8)PE0), U3.3 ((TXD0)PE1), U3.11 (GND), U3.30 (RESET), U3.32, U3.43 ((SCL/INT0)PD0), U3.44 ((SDA/INT1)PD1), U3.62, U3.81, U3.99 (AGND), U4.1 (VIN), U4.2 (GND), U4.3 (ON/~OFF), U5.1 (GND), U5.2 (VOUT), U5.4 (VOUT__1), U6.1 (XTAL1), U6.2 (PC0/XTAL2), U6.3 (GND), U6.4 (VCC), U6.8 (PD2), U6.9 (PD3), U6.13 (~HWB/PD7), U6.28 (UGND), U6.32 (AVCC), Y1.2, Y2.1, Y2.2, YELLOW1.2 (A), YELLOW2.2 (A)
/8PB4: J10.1, U6.18 (PB4)
/8PB5: J10.3, U6.19 (PB5)
/8PB6: J10.2, U6.20 (PB6)
/8PB7: J10.4, U6.21 (PB7)
/ADC0: J5.1, U3.97 ((ADC0)PF0)
/ADC1: J5.2, U3.96 ((ADC1)PF1)
/ADC2: J5.3, U3.95 ((ADC2)PF2)
/ADC3: J5.4, U3.94 ((ADC3)PF3)
/ADC4: J5.5, U3.93 ((ADC4/TCK)PF4)
/ADC5: J5.6, U3.92 ((ADC5/TMS)PF5)
/ADC6: J5.7, U3.91 ((ADC6/TDO)PF6)
/ADC7: J5.8, U3.90 ((ADC7/TDI)PF7)
/ADC8: J2.8, U3.89 (PK0(ADC8/PCINT16))
/ADC9: J2.7, U3.88 (PK1(ADC9/PCINT17))
/ADC10: J2.6, U3.87 (PK2(ADC10/PCINT18))
/ADC11: J2.5, U3.86 (PK3(ADC11/PCINT19))
/ADC12: J2.4, U3.85 (PK4(ADC12/PCINT20))
/ADC13: J2.3, U3.84 (PK5(ADC13/PCINT21))
/ADC14: J2.2, U3.83 (PK6(ADC14/PCINT22))
/ADC15: J2.1, U3.82 (PK7(ADC15/PCINT23))
/AREF: C5.1, J6.3, U3.98 (AREF)
/AVCC: C3.1, L1.1, U3.100 (AVCC)
/D+: J12.3 (D+), R21.1, RV1.1
/D-: J12.2 (D-), R20.1, RV2.1
/GATE_CMD: U1.7, U2.1 (G)
/MISO2: D4.1 (K), J11.1, J11.5, R18.1, U6.17 (PB3), U6.24 (PC1/~RESET)
/MOSI2: J11.4, U6.16 (PB2)
/PA0: J7.3, U3.78 ((AD0)PA0)
/PA1: J7.4, U3.77 ((AD1)PA1)
/PA2: J7.5, U3.76 ((AD2)PA2)
/PA3: J7.6, U3.75 ((AD3)PA3)
/PA4: J7.7, U3.74 ((AD4)PA4)
/PA5: J7.8, U3.73 ((AD5)PA5)
/PA6: J7.9, U3.72 ((AD6)PA6)
/PA7: J7.10, U3.71 ((AD7)PA7)
/PB0: J7.34, U3.19 ((SS/PCINT0)PB0)
/PB1: J7.33, J8.3, U3.20 ((SCK/PCINT1)PB1)
/PB2: J7.32, J8.4, U3.21 ((MOSI/PCINT2)PB2)
/PB3: J7.31, J8.1, U3.22 ((MISO/PCINT3)PB3)
/PB4: J6.8, U3.23 ((OC2A/PCINT4)PB4)
/PB5: J6.7, U3.24 ((OC1A/PCINT5)PB5)
/PB6: J6.6, U3.25 ((OC1B/PCINT6)PB6)
/PB7: J6.5, U1.3 (+), U3.26 ((OC0A/OC1C/PCINT7)PB7)
/PC0: J7.18, U3.53 ((A8)PC0)
/PC1: J7.17, U3.54 ((A9)PC1)
/PC2: J7.16, U3.55 ((A10)PC2)
/PC3: J7.15, U3.56 ((A11)PC3)
/PC4: J7.14, U3.57 ((A12)PC4)
/PC5: J7.13, U3.58 ((A13)PC5)
/PC6: J7.12, U3.59 ((A14)PC6)
/PC7: J7.11, U3.60 ((A15)PC7)
/PD7: J7.19, U3.50 ((T0)PD7)
/PE3: J4.6, U3.5 ((OC3A/AIN1)PE3)
/PE4: J4.3, J4.4, J4.5, U3.1 ((OC0B)PG5), U3.6 ((OC3B/INT4)PE4), U3.7 ((OC3C/INT5)PE5)
/PG0: J7.22, U3.51 ((WR)PG0)
/PG1: J7.21, U3.52 ((RD)PG1)
/PG2: J7.20, U3.70 ((ALE)PG2)
/PH3: J4.7, U3.15 (PH3(OC4A))
/PH4: J4.8, U3.16 (PH4(OC4B))
/PH5: J6.10, U3.17 (PH5(OC4C))
/PH6: J6.9, U3.18 (PH6(OC2B))
/PL0: J7.30, U3.35 (PL0(ICP4))
/PL1: J7.29, U3.36 (PL1(ICP5))
/PL2: J7.28, U3.37 (PL2(T5))
/PL3: J7.27, U3.38 (PL3(OC5A))
/PL4: J7.26, U3.39 (PL4(OC5B))
/PL5: J7.25, U3.40 (PL5(OC5C))
/PL6: J7.24, U3.41 (PL6)
/PL7: J7.23, U3.42 (PL7)
/RD+: R21.2, U6.29 (D+)
/RD-: R20.2, U6.30 (D-)
/RXD1: J3.3, U3.45 ((RXD1/INT2)PD2)
/RXD2: J3.5, U3.12 (PH0(RXD2))
/RXD3: J3.7, U3.63 (PJ0(RXD3/PCINT9))
/RXL: U6.10 (PD4), YELLOW2.1 (K)
/SCK2: J11.3, U6.15 (PB1)
/TXD1: J3.4, U3.46 ((TXD1/INT3)PD3)
/TXD2: J3.6, U3.13 (PH1(TXD2))
/TXD3: J3.8, U3.64 (PJ1(TXD3/PCINT10))
/TXL: U6.11 (PD5), YELLOW1.1 (K)
/USBVCC: C16.1, F1.2, U2.3 (D), U6.31 (UVCC)
/USHIELD: FB1.2, J12.5 (Shield), RV1.2, RV2.2
/XTAL1: R3.2, U3.34 (XTAL1), Y1.3
/XTAL2: R3.1, U3.33 (XTAL2), Y1.1
/XVCC: F1.1, J12.1 (VBUS)
unnamed: D3.C, J9.2
unnamed: C4.1, C6.1, C7.1, L1.2, U3.10 (VCC), U3.31, U3.61, U3.80
unnamed: C10.1, C11.1, D3.A, U5.3 (VIN)
unnamed: C15.2, U6.27 (UCAP)

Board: 2 copper layers, 75 parts (0 on the bottom side), 91 nets, no tracks yet.

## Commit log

2024-07-08 updated schematic project
2024-07-11 done more work on schematic
2024-07-11 halfway through labelling
2024-07-12 finished the schematic without mpower supply
2024-07-12 my potential final schematic
2024-07-12 remaining with mh2029, the two connectors to finish footprint assignment
2024-07-12 finished editing the schematic and assigning footprints
2024-07-13 started PCB design
2024-07-15 last save attempt
2024-07-15 final top layer
2024-07-16 finished ratsnests connections
2024-07-19 instance before beginning to edit
2024-07-22 good progress
2024-07-24 final edit
2024-07-25 almost final
2024-08-01 to edit in onshape
2024-08-08 hardest trial
2024-08-12 correction on pcb layout
2024-08-12 hopefully the final pcb layout
